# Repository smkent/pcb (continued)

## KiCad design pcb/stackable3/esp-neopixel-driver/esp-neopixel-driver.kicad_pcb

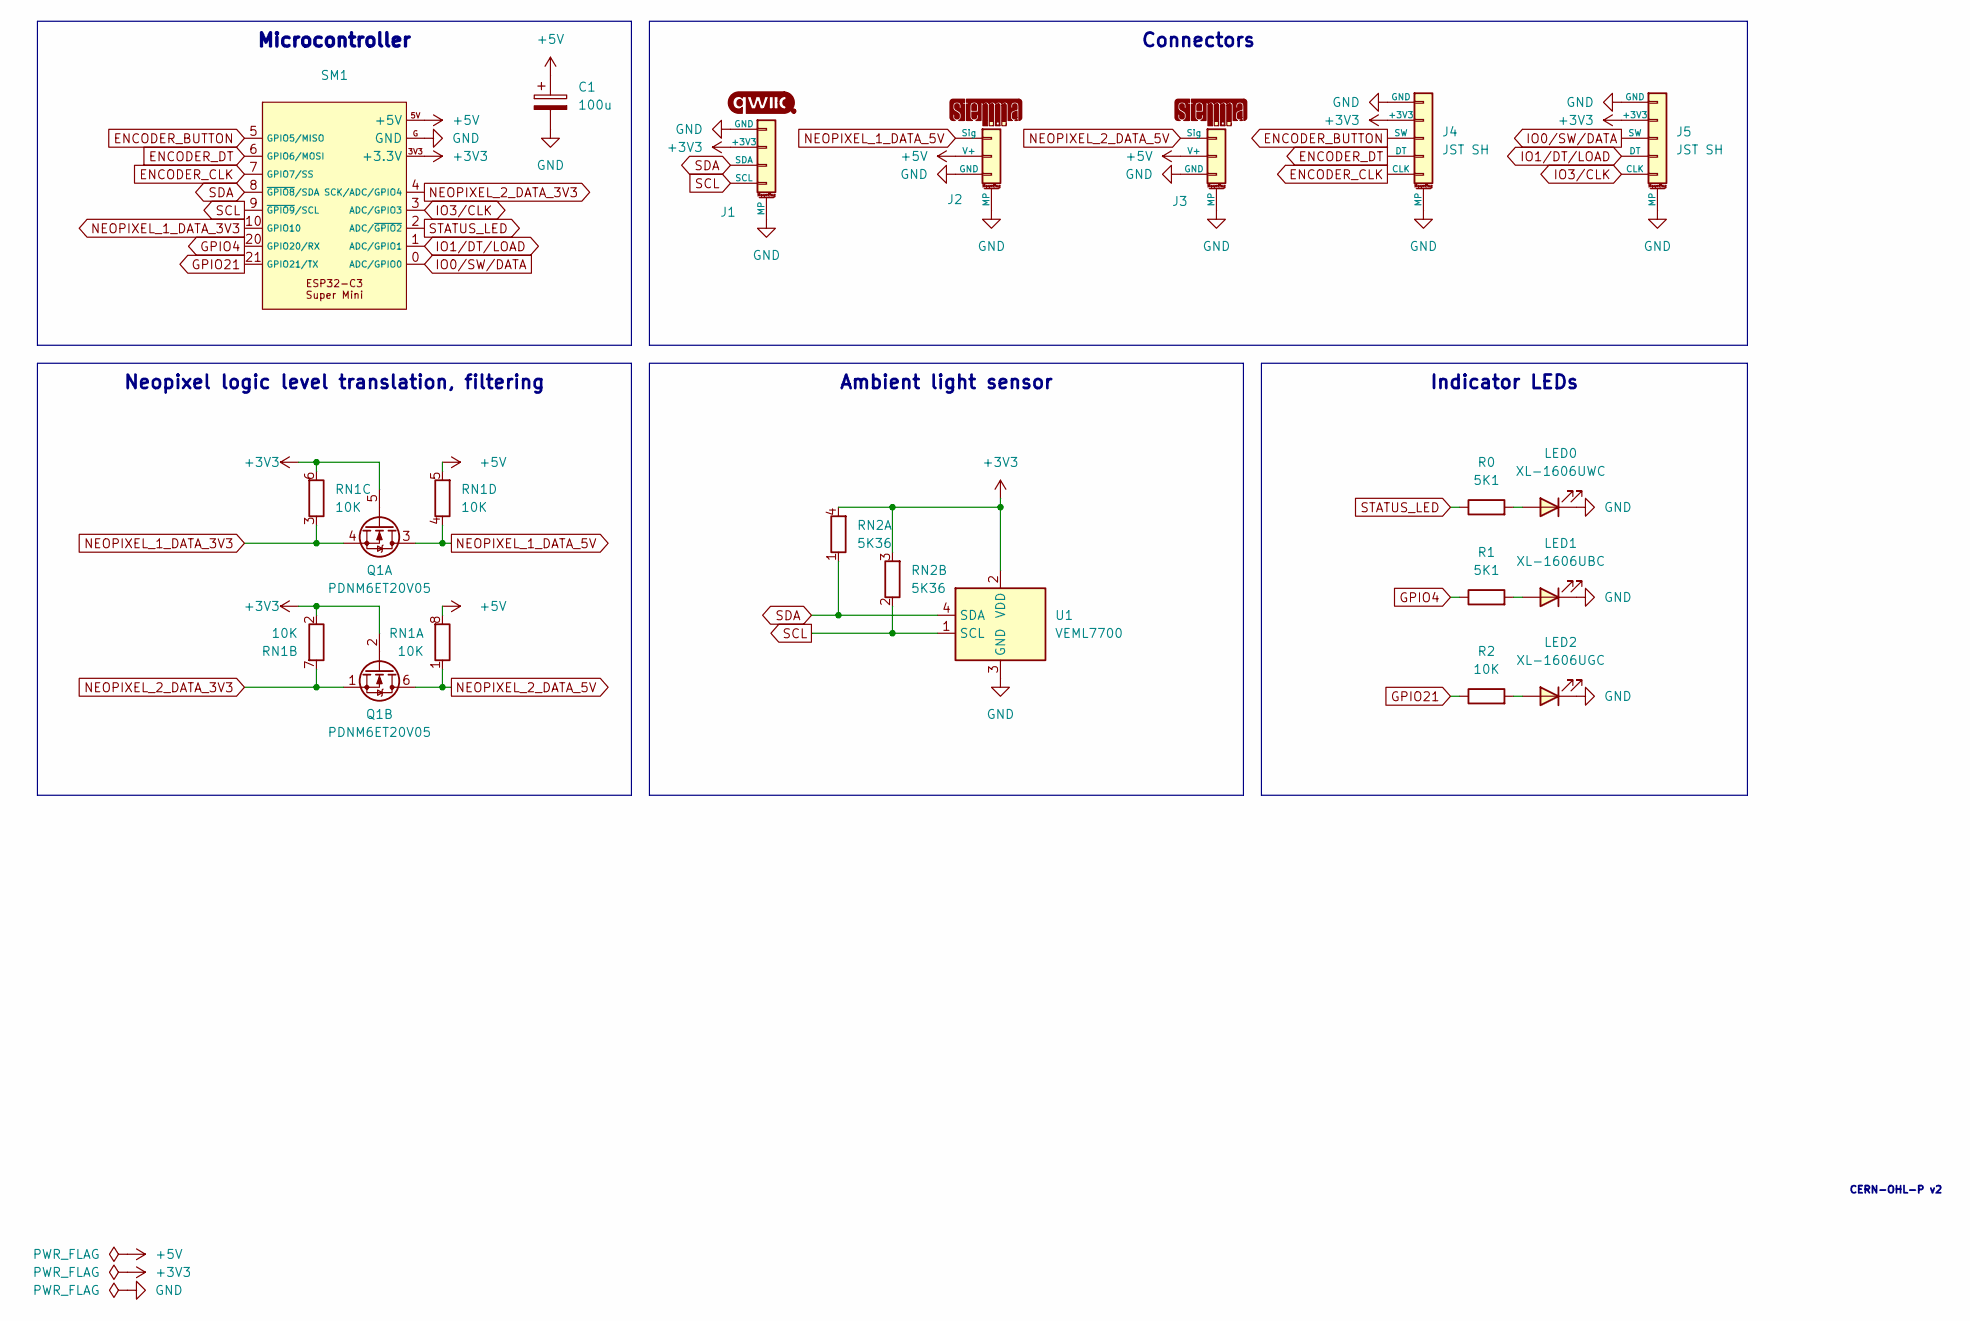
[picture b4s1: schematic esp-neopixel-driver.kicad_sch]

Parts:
C1: 100u; CP_Elec_5x5.4; LCSC Part C4054379
J1: Qwiic; Qwiic-SMD-horizontal-logo; LCSC Part C19270571
J2, J3: STEMMA-Signal; STEMMA-Signal-SMD-horizontal; LCSC Part C5372880
J4, J5: JST SH; JST_SH_SM05B-SRSS-TB_1x05-1MP_P1.00mm_Horizontal; LCSC Part C7433426
LED0: XL-1606UWC; LED_SideEmitter_1.7x1.1mm; LCSC Part C965866
LED1: XL-1606UBC; LED_SideEmitter_1.7x1.1mm; LCSC Part C965865
LED2: XL-1606UGC; LED_SideEmitter_1.7x1.1mm; LCSC Part C965863
Q1: PDNM6ET20V05; SOT-563; LCSC Part C918811
R0, R1: 5K1; R_0402_1005Metric; LCSC Part C25905
R2: 10K; R_0402_1005Metric; LCSC Part C25744
RN1: 10K; R_Array_Convex_4x0402; LCSC Part C7422173
RN2: 5K36; R_Array_Convex_2x0402; LCSC Part C425352
SM1: ESP32-C3-Super-Mini-Castellated-SMD-only
U1: VEML7700; Sensor_VEML7700-TR; LCSC Part C504893

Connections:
+3V3: J1.2 (+3V3), J4.2 (+3V3), J5.2 (+3V3), Q1.2 (G), Q1.5 (G), RN1.2 (R2.1), RN1.6 (R3.2), RN2.3 (R2.2), RN2.4 (R1.2), SM1.3V3 (+3.3V), U1.2 (VDD)
+5V: C1.1, J2.2 (V+), J3.2 (V+), RN1.5 (R4.2), RN1.8 (R1.2), SM1.5V (+5V)
ENCODER_BUTTON: J4.3 (SW), SM1.5 (GPIO5/MISO)
ENCODER_CLK: J4.5 (CLK), SM1.7 (GPIO7/SS)
ENCODER_DT: J4.4 (DT), SM1.6 (GPIO6/MOSI)
GND: C1.2, J1.1 (GND), J1.MP, J2.3 (GND), J2.MP, J3.3 (GND), J3.MP, J4.1 (GND), J4.MP, J5.1 (GND), J5.MP, LED0.1 (K), LED1.1 (K), LED2.1 (K), SM1.G (GND), U1.3 (GND)
GPIO4: R1.1, SM1.20 (GPIO20/RX)
GPIO21: R2.1, SM1.21 (GPIO21/TX)
IO0/SW/DATA: J5.3 (SW), SM1.0 (ADC/GPIO0)
IO1/DT/LOAD: J5.4 (DT), SM1.1 (ADC/GPIO1)
IO3/CLK: J5.5 (CLK), SM1.3 (ADC/GPIO3)
NEOPIXEL_1_DATA_3V3: Q1.4 (S), RN1.3 (R3.1), SM1.10 (GPIO10)
NEOPIXEL_1_DATA_5V: J2.1 (Sig), Q1.3 (D), RN1.4 (R4.1)
NEOPIXEL_2_DATA_3V3: Q1.1 (S), RN1.7 (R2.2), SM1.4 (SCK/ADC/GPIO4)
NEOPIXEL_2_DATA_5V: J3.1 (Sig), Q1.6 (D), RN1.1 (R1.1)
unnamed: LED0.2 (A), R0.2
unnamed: LED1.2 (A), R1.2
unnamed: LED2.2 (A), R2.2
SCL: J1.4 (SCL), RN2.2 (R2.1), SM1.9 (~GPIO9/SCL), U1.1 (SCL)
SDA: J1.3 (SDA), RN2.1 (R1.1), SM1.8 (~GPIO8/SDA), U1.4 (SDA)
STATUS_LED: R0.1, SM1.2 (ADC/~GPIO2)

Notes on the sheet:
Ambient light sensor
Connectors
Neopixel logic level translation, filtering
Indicator LEDs
Microcontroller
CERN-OHL-P v2

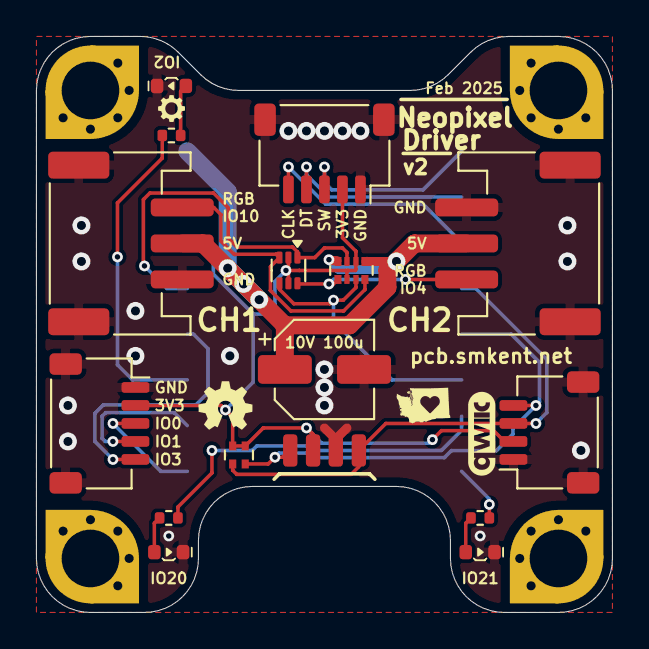
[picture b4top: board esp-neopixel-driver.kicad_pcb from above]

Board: 2 copper layers, 32.0 x 32.0 mm, 17 parts (1 on the bottom side), 21 nets.

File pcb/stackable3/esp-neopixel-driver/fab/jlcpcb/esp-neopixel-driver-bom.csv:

Comment,Designator,Footprint,LCSC
JST SH,"J4,J5",connector:JST_SH_SM05B-SRSS-TB_1x05-1MP_P1.00mm_Horizontal,C7433426
5K1,"R0,R1",Resistor_SMD:R_0402_1005Metric,C25905
XL-1606UWC,LED0,discrete:LED_SideEmitter_1.7x1.1mm,C965866
100u,C1,Capacitor_SMD:CP_Elec_5x5.4,C4054379
XL-1606UGC,LED2,discrete:LED_SideEmitter_1.7x1.1mm,C965863
Qwiic,J1,connector:Qwiic-SMD-horizontal-logo,C19270571
~,SM1,module:ESP32-C3-Super-Mini-Castellated-SMD-only,
5K36,RN2,Resistor_SMD:R_Array_Convex_2x0402, C425352
XL-1606UBC,LED1,discrete:LED_SideEmitter_1.7x1.1mm,C965865
10K,RN1,Resistor_SMD:R_Array_Convex_4x0402,C7422173
STEMMA-Signal,"J2,J3",connector:STEMMA-Signal-SMD-horizontal,C5372880
PDNM6ET20V05,Q1,Package_TO_SOT_SMD:SOT-563,C918811
VEML7700,U1,discrete:Sensor_VEML7700-TR,C504893
10K,R2,Resistor_SMD:R_0402_1005Metric,C25744

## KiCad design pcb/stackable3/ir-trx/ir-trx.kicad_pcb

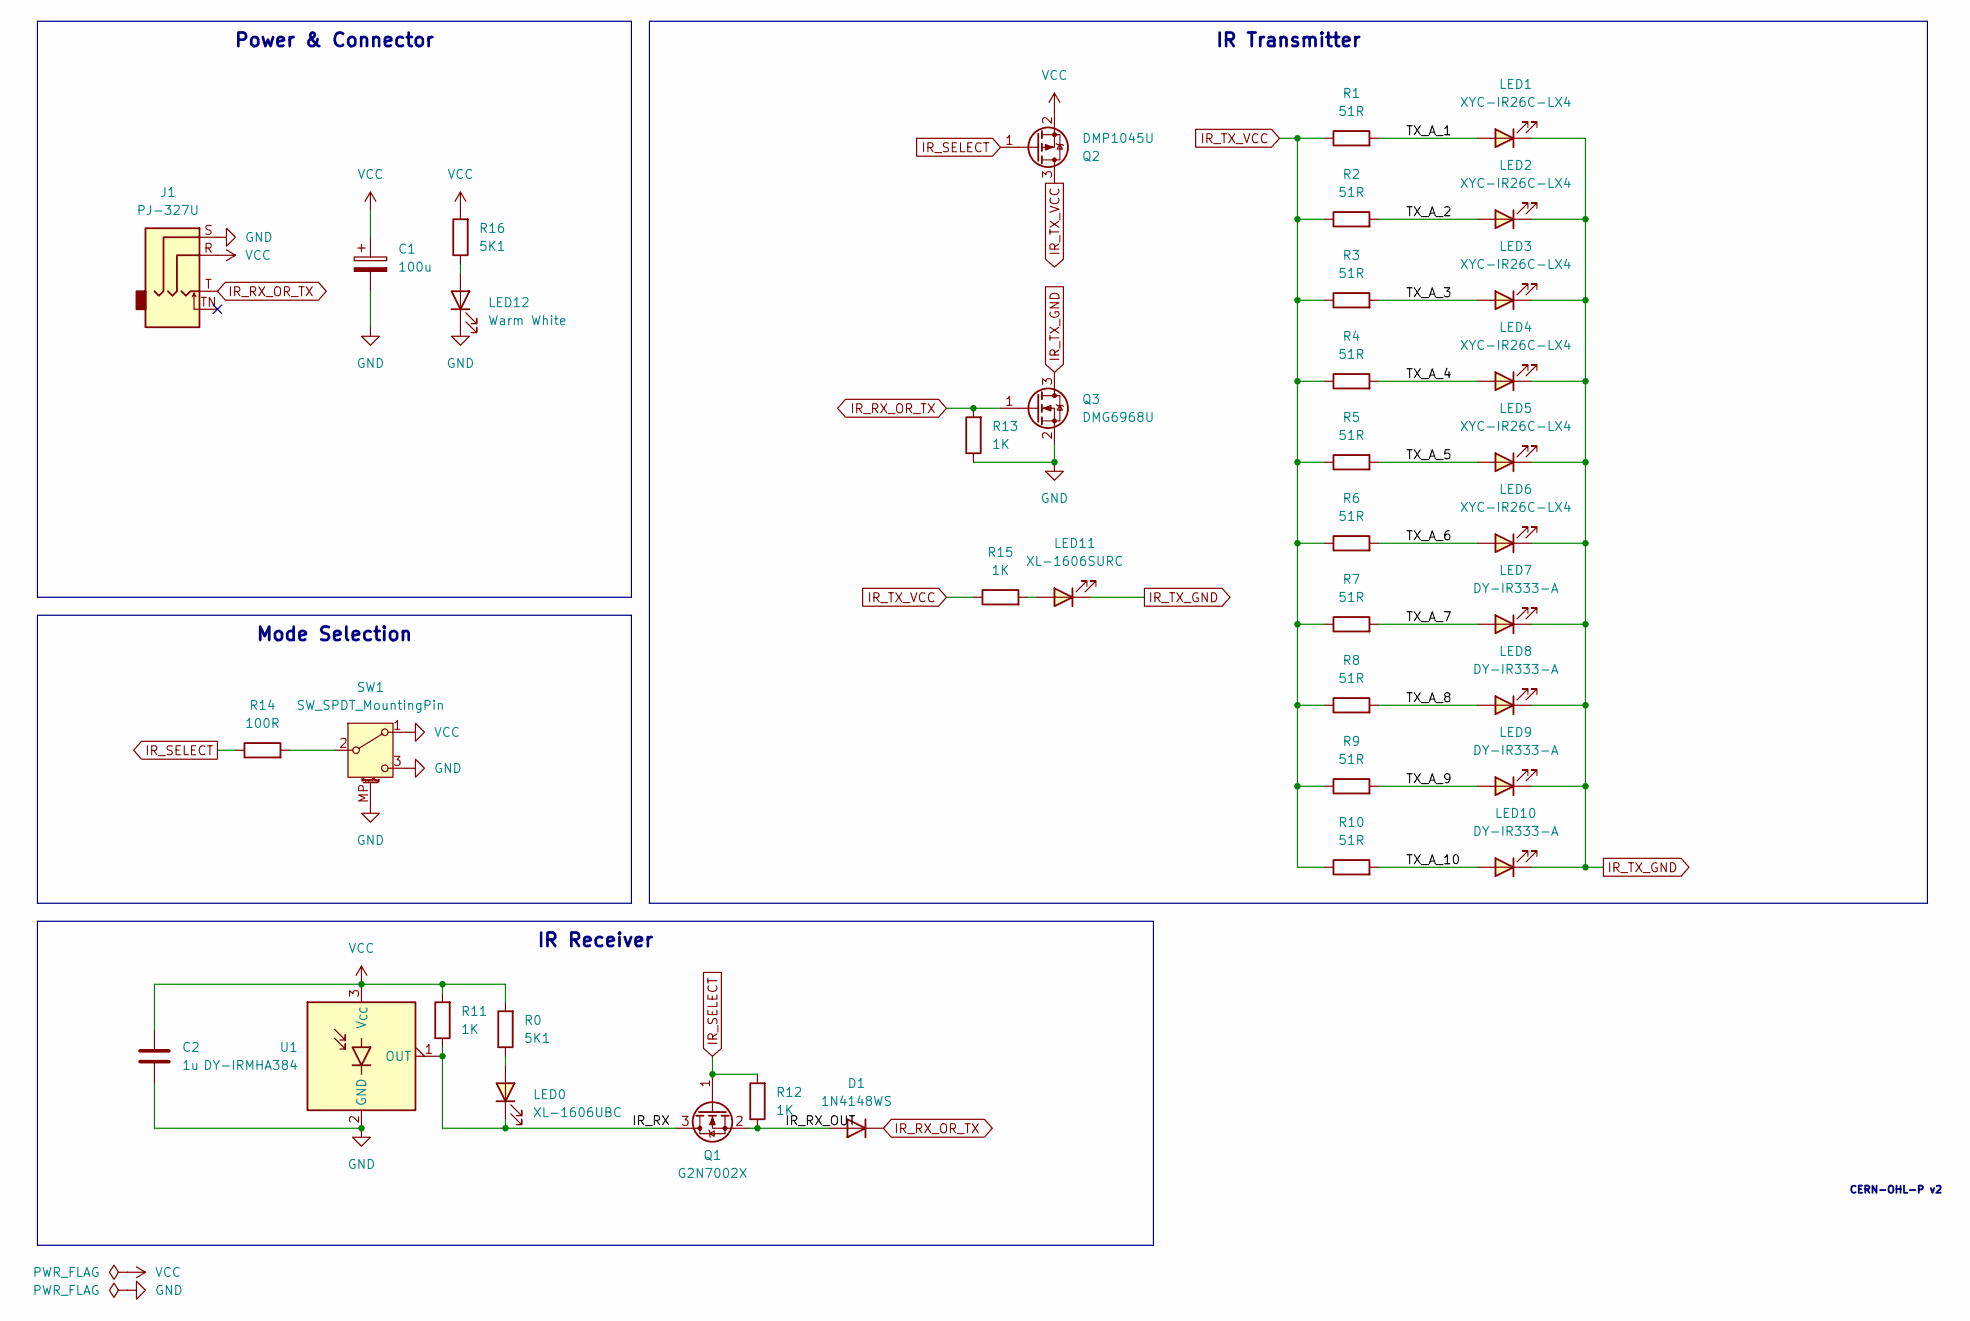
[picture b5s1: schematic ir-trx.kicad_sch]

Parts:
C1: 100u; CP_Elec_5x5.4
C2: 1u; C_0402_1005Metric
D1: 1N4148WS; D_SOD-323
J1: PJ-327U; Jack_3.5mm_PJ-327U-SMT_Horizontal_EdgeCut; LCSC Part C397453
LED0: XL-1606UBC; LED_SideEmitter_1.7x1.1mm; LCSC Part C965865
LED1, LED2, LED3, LED4, LED5, LED6: XYC-IR26C-LX4; LED_IR_SideEmitter_1206_3216Metric; LCSC Part C396674
LED7, LED8, LED9, LED10: DY-IR333-A; LED_D5.0mm_IRGrey; LCSC Part C396674
LED11: XL-1606SURC; LED_SideEmitter_1.7x1.1mm; LCSC Part C965860
LED12: Warm White; LED_0603_1608Metric
Q1: G2N7002X; SOT-523; LCSC Part C5258971
Q2: DMP1045U; SOT-23; LCSC Part C177033
Q3: DMG6968U; SOT-23; LCSC Part C150759
R0, R16: 5K1; R_0402_1005Metric
R1, R2, R3, R4, R5, R6, R7, R8, R9, R10: 51R; R_1206_3216Metric
R11, R12, R13, R15: 1K; R_0402_1005Metric
R14: 100R; R_0603_1608Metric
SW1: SW_SPDT_MountingPin; SW_Slide_SPDT_Straight_CK_OS102011MS2Q
U1: DY-IRMHA384; IRM_5.0mmx4.2mm_P1.27mm_Horizontal; LCSC Part C6071554

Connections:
/IR_RX: LED0.1 (K), Q1.3 (D), R11.1, U1.1 (OUT)
/IR_RX_OUT: D1.2 (A), Q1.2 (S), R12.1
/TX_A_1: LED1.2 (A), R1.2
/TX_A_2: LED2.2 (A), R2.2
/TX_A_3: LED3.2 (A), R3.2
/TX_A_4: LED4.2 (A), R4.2
/TX_A_5: LED5.2 (A), R5.2
/TX_A_6: LED6.2 (A), R6.2
/TX_A_7: LED7.2 (A), R7.2
/TX_A_8: LED8.2 (A), R8.2
/TX_A_9: LED9.2 (A), R9.2
/TX_A_10: LED10.2 (A), R10.2
GND: C1.2, C2.2, J1.S, LED12.1 (K), Q3.2 (S), R13.1, SW1.3 (C), SW1.MP (MountPin), U1.2 (GND)
IR_RX_OR_TX: D1.1 (K), J1.T, Q3.1 (G), R13.2
IR_SELECT: Q1.1 (G), Q2.1 (G), R12.2, R14.1
IR_TX_GND: LED1.1 (K), LED2.1 (K), LED3.1 (K), LED4.1 (K), LED5.1 (K), LED6.1 (K), LED7.1 (K), LED8.1 (K), LED9.1 (K), LED10.1 (K), LED11.1 (K), Q3.3 (D)
IR_TX_VCC: Q2.3 (D), R1.1, R2.1, R3.1, R4.1, R5.1, R6.1, R7.1, R8.1, R9.1, R10.1, R15.1
unnamed: LED0.2 (A), R0.1
unnamed: LED11.2 (A), R15.2
unnamed: LED12.2 (A), R16.1
unnamed: R14.2, SW1.2 (B)
VCC: C1.1, C2.1, J1.R, Q2.2 (S), R0.2, R11.2, R16.2, SW1.1 (A), U1.3 (V_{CC})

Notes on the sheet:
Power & Connector
Mode Selection
IR Receiver
IR Transmitter
CERN-OHL-P v2

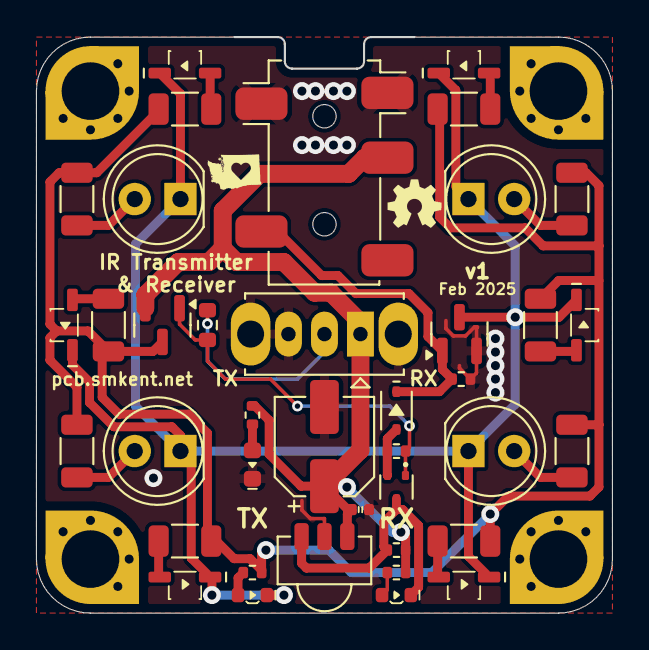
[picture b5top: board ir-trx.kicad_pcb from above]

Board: 2 copper layers, 32.0 x 32.0 mm, 39 parts (0 on the bottom side), 22 nets.

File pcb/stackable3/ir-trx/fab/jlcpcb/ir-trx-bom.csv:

Comment,Designator,Footprint,LCSC
51R,"R1,R2,R3,R4,R5,R6,R7,R8,R9,R10",Resistor_SMD:R_1206_3216Metric,C149687
PJ-327U,J1,connector:Jack_3.5mm_PJ-327U-SMT_Horizontal_EdgeCut,C397453
1N4148WS,D1,package:D_SOD-323,
SW_SPDT_MountingPin,SW1,electromechanical:SW_Slide_SPDT_Straight_CK_OS102011MS2Q,
DMG6968U,Q3,Package_TO_SOT_SMD:SOT-23,C150759
1K,"R11,R12,R13,R15",Resistor_SMD:R_0402_1005Metric,
DY-IR333-A,"LED7,LED8,LED9,LED10",LED_THT:LED_D5.0mm_IRGrey,C396674
DMP1045U,Q2,Package_TO_SOT_SMD:SOT-23,C177033
100u,C1,Capacitor_SMD:CP_Elec_5x5.4,
G2N7002X,Q1,package:SOT-523,C5258971
DY-IRMHA384,U1,package:IRM_5.0mmx4.2mm_P1.27mm_Horizontal,C6071554
XL-1606SURC,LED11,discrete:LED_SideEmitter_1.7x1.1mm,C965860
100R,R14,Resistor_SMD:R_0603_1608Metric,
5K1,"R0,R16",Resistor_SMD:R_0402_1005Metric,
XYC-IR26C-LX4,"LED1,LED2,LED3,LED4,LED5,LED6",discrete:LED_IR_SideEmitter_1206_3216Metric,C396674
XL-1606UBC,LED0,discrete:LED_SideEmitter_1.7x1.1mm,C965865
Warm White,LED12,discrete:LED_0603_1608Metric,
1u,C2,discrete:C_0402_1005Metric,

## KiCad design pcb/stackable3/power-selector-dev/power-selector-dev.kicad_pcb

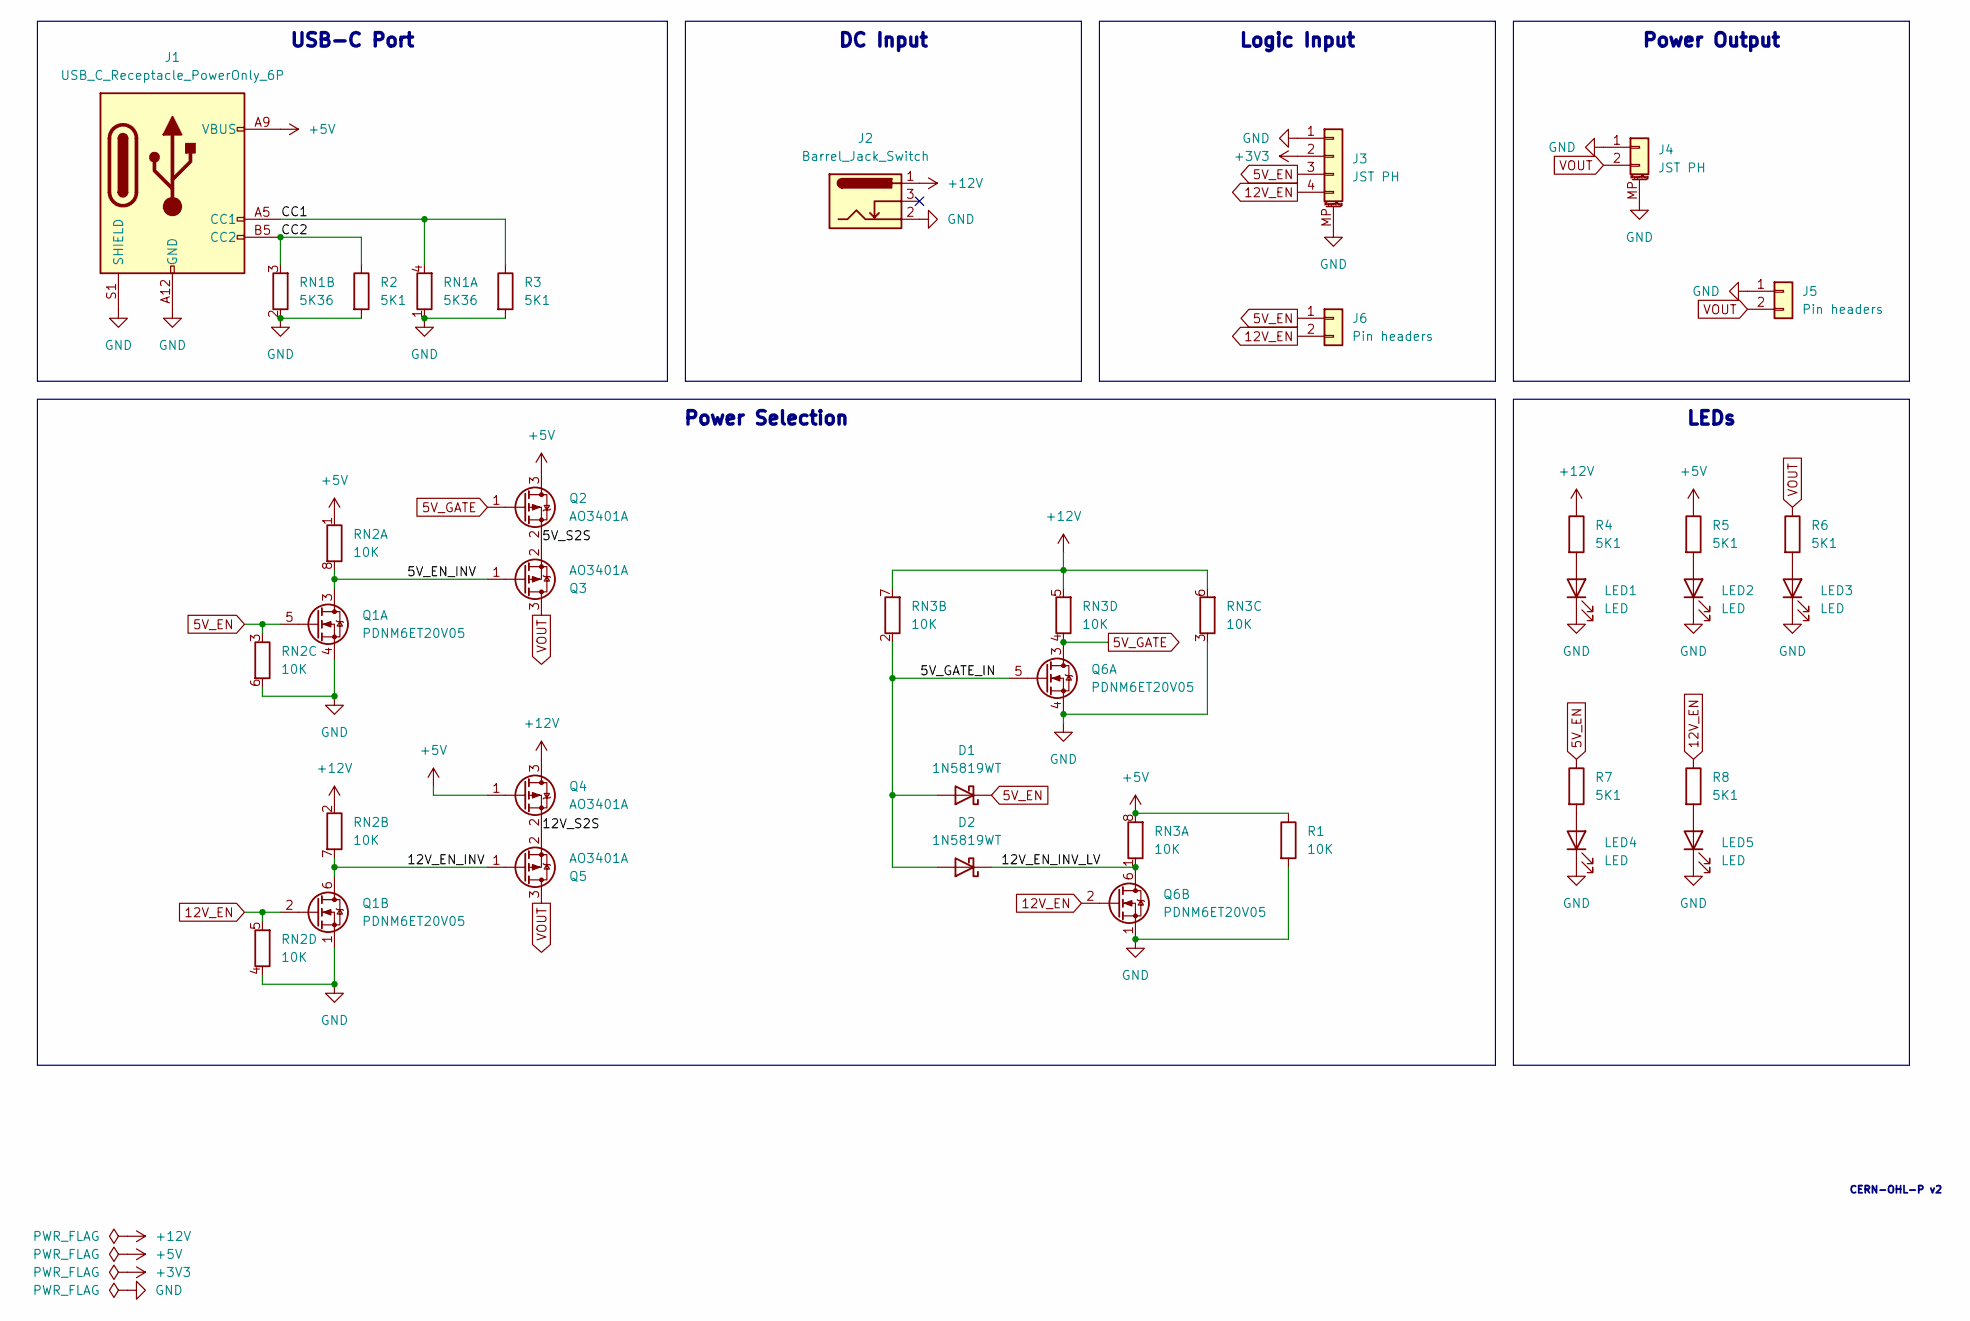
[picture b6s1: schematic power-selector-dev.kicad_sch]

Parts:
D1, D2: 1N5819WT; D_SOD-523; LCSC Part C20754784
J1: USB_C_Receptacle_PowerOnly_6P; USB_C_Receptacle_GCT_USB4125-xx-x_6P_TopMnt_Horizontal_Hand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; LCSC Part C2927029
J2: Barrel_Jack_Switch; BarrelJack_DC-050_SMT_Horizontal
J3: JST PH; JST_PH_S4B-PH-SM4-TB_1x04-1MP_P2.00mm_Horizontal
J4: JST PH; JST_PH_S2B-PH-SM4-TB_1x02-1MP_P2.00mm_Horizontal
J5, J6: Pin headers; PinHeader_1x02_P2.54mm_Vertical_simple
LED1, LED2, LED3, LED4, LED5: LED; LED_0603_1608Metric
Q1, Q6: PDNM6ET20V05; SOT-563; LCSC Part C918811
Q2, Q3, Q4, Q5: AO3401A; SOT-23
R1: 10K; R_0402_1005Metric
R2, R3, R4, R5, R6: 5K1; R_0603_1608Metric
R7, R8: 5K1; R_0402_1005Metric
RN1: 5K36; R_Array_Convex_2x0402
RN2, RN3: 10K; R_Array_Convex_4x0402

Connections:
5V_EN: D1.1 (K), J3.3, J6.1, Q1.5 (G), R7.1, RN2.3 (R3.1)
5V_GATE: Q2.1 (G), Q6.3 (D), RN3.4 (R4.1)
12V_EN: J3.4, J6.2, Q1.2 (G), Q6.2 (G), R8.1, RN2.5 (R4.2)
+3V3: J3.2
+5V: J1.A9 (VBUS), J1.B9 (VBUS), Q2.3 (D), Q4.1 (G), R1.1, R5.1, RN2.1 (R1.1), RN3.8 (R1.2)
+12V: J2.1, Q4.3 (D), R4.1, RN2.2 (R2.1), RN3.5 (R4.2), RN3.6 (R3.2), RN3.7 (R2.2)
/5V_EN_INV: Q1.3 (D), Q3.1 (G), RN2.8 (R1.2)
/5V_GATE_IN: D1.2 (A), D2.2 (A), Q6.5 (G), RN3.2 (R2.1)
/5V_S2S: Q2.2 (S), Q3.2 (S)
/12V_EN_INV: Q1.6 (D), Q5.1 (G), RN2.7 (R2.2)
/12V_EN_INV_LV: D2.1 (K), Q6.6 (D), RN3.1 (R1.1)
/12V_S2S: Q4.2 (S), Q5.2 (S)
/CC1: J1.A5 (CC1), R3.1, RN1.4 (R1.2)
/CC2: J1.B5 (CC2), R2.1, RN1.3 (R2.2)
GND: J1.A12 (GND), J1.B12 (GND), J1.S1 (SHIELD), J2.2, J3.1, J3.MP (MountPin), J4.1, J4.MP (MountPin), J5.1, LED1.1 (K), LED2.1 (K), LED3.1 (K), LED4.1 (K), LED5.1 (K), Q1.1 (S), Q1.4 (S), Q6.1 (S), Q6.4 (S), R1.2, R2.2, R3.2, RN1.1 (R1.1), RN1.2 (R2.1), RN2.4 (R4.1), RN2.6 (R3.2), RN3.3 (R3.1)
unnamed: LED1.2 (A), R4.2
unnamed: LED2.2 (A), R5.2
unnamed: LED3.2 (A), R6.2
unnamed: LED4.2 (A), R7.2
unnamed: LED5.2 (A), R8.2
VOUT: J4.2, J5.2, Q3.3 (D), Q5.3 (D), R6.1

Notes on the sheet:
Logic Input
DC Input
Power Output
USB-C Port
Power Selection
LEDs
CERN-OHL-P v2

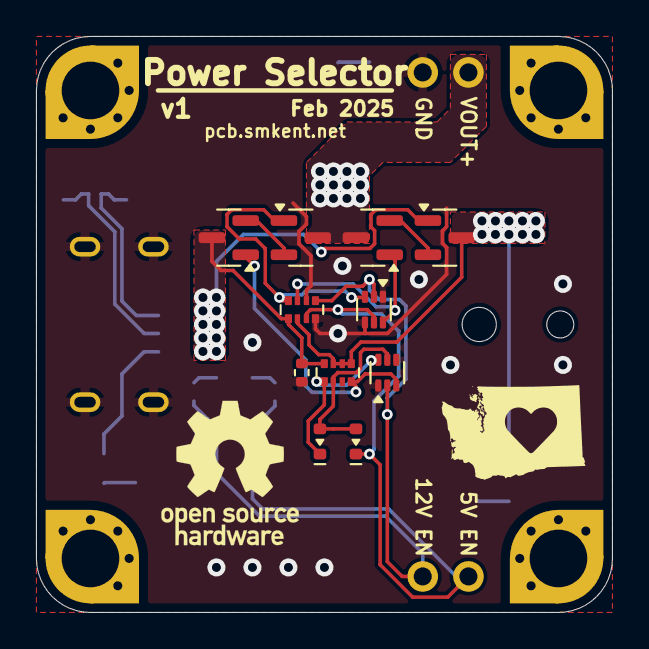
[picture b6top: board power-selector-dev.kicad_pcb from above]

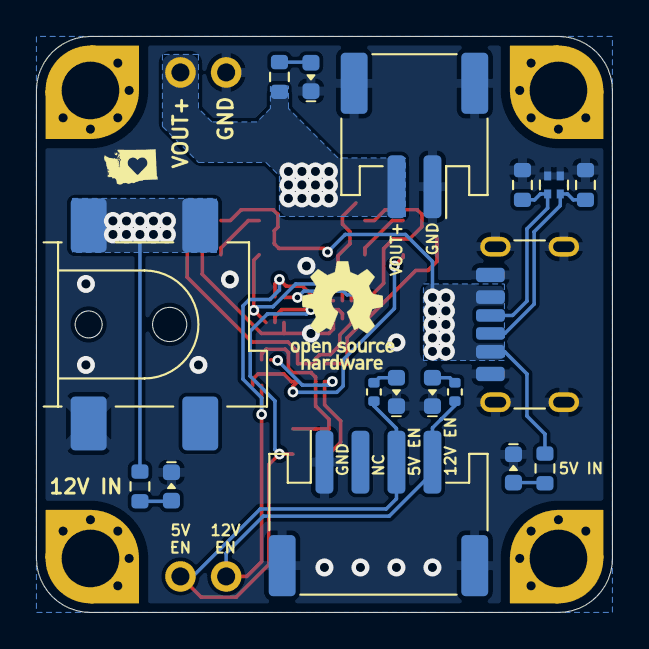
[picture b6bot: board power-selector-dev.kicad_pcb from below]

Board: 2 copper layers, 32.0 x 32.0 mm, 30 parts (19 on the bottom side), 20 nets.

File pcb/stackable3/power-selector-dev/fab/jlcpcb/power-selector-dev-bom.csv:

Comment,Designator,Footprint,LCSC
5K1,"R7,R8",Resistor_SMD:R_0402_1005Metric,
PDNM6ET20V05,"Q1,Q6",Package_TO_SOT_SMD:SOT-563,C918811
10K,"RN2,RN3",discrete:R_Array_Convex_4x0402,
1N5819WT,"D1,D2",package:D_SOD-523,C20754784
Barrel_Jack_Switch,J2,connector:BarrelJack_DC-050_SMT_Horizontal,
5K1,"R2,R3,R4,R5,R6",Resistor_SMD:R_0603_1608Metric,
LED,"LED1,LED2,LED3,LED4,LED5",discrete:LED_0603_1608Metric,
Pin headers,"J5,J6",custom:PinHeader_1x02_P2.54mm_Vertical_simple,
10K,R1,Resistor_SMD:R_0402_1005Metric,
AO3401A,"Q2,Q3,Q4,Q5",Package_TO_SOT_SMD:SOT-23,
USB_C_Receptacle_PowerOnly_6P,J1,connector:USB_C_Receptacle_GCT_USB4125-xx-x_6P_TopMnt_Horizontal_HandSolder,C2927029
JST PH,J4,connector:JST_PH_S2B-PH-SM4-TB_1x02-1MP_P2.00mm_Horizontal,
JST PH,J3,connector:JST_PH_S4B-PH-SM4-TB_1x04-1MP_P2.00mm_Horizontal,
5K36,RN1,Resistor_SMD:R_Array_Convex_2x0402,

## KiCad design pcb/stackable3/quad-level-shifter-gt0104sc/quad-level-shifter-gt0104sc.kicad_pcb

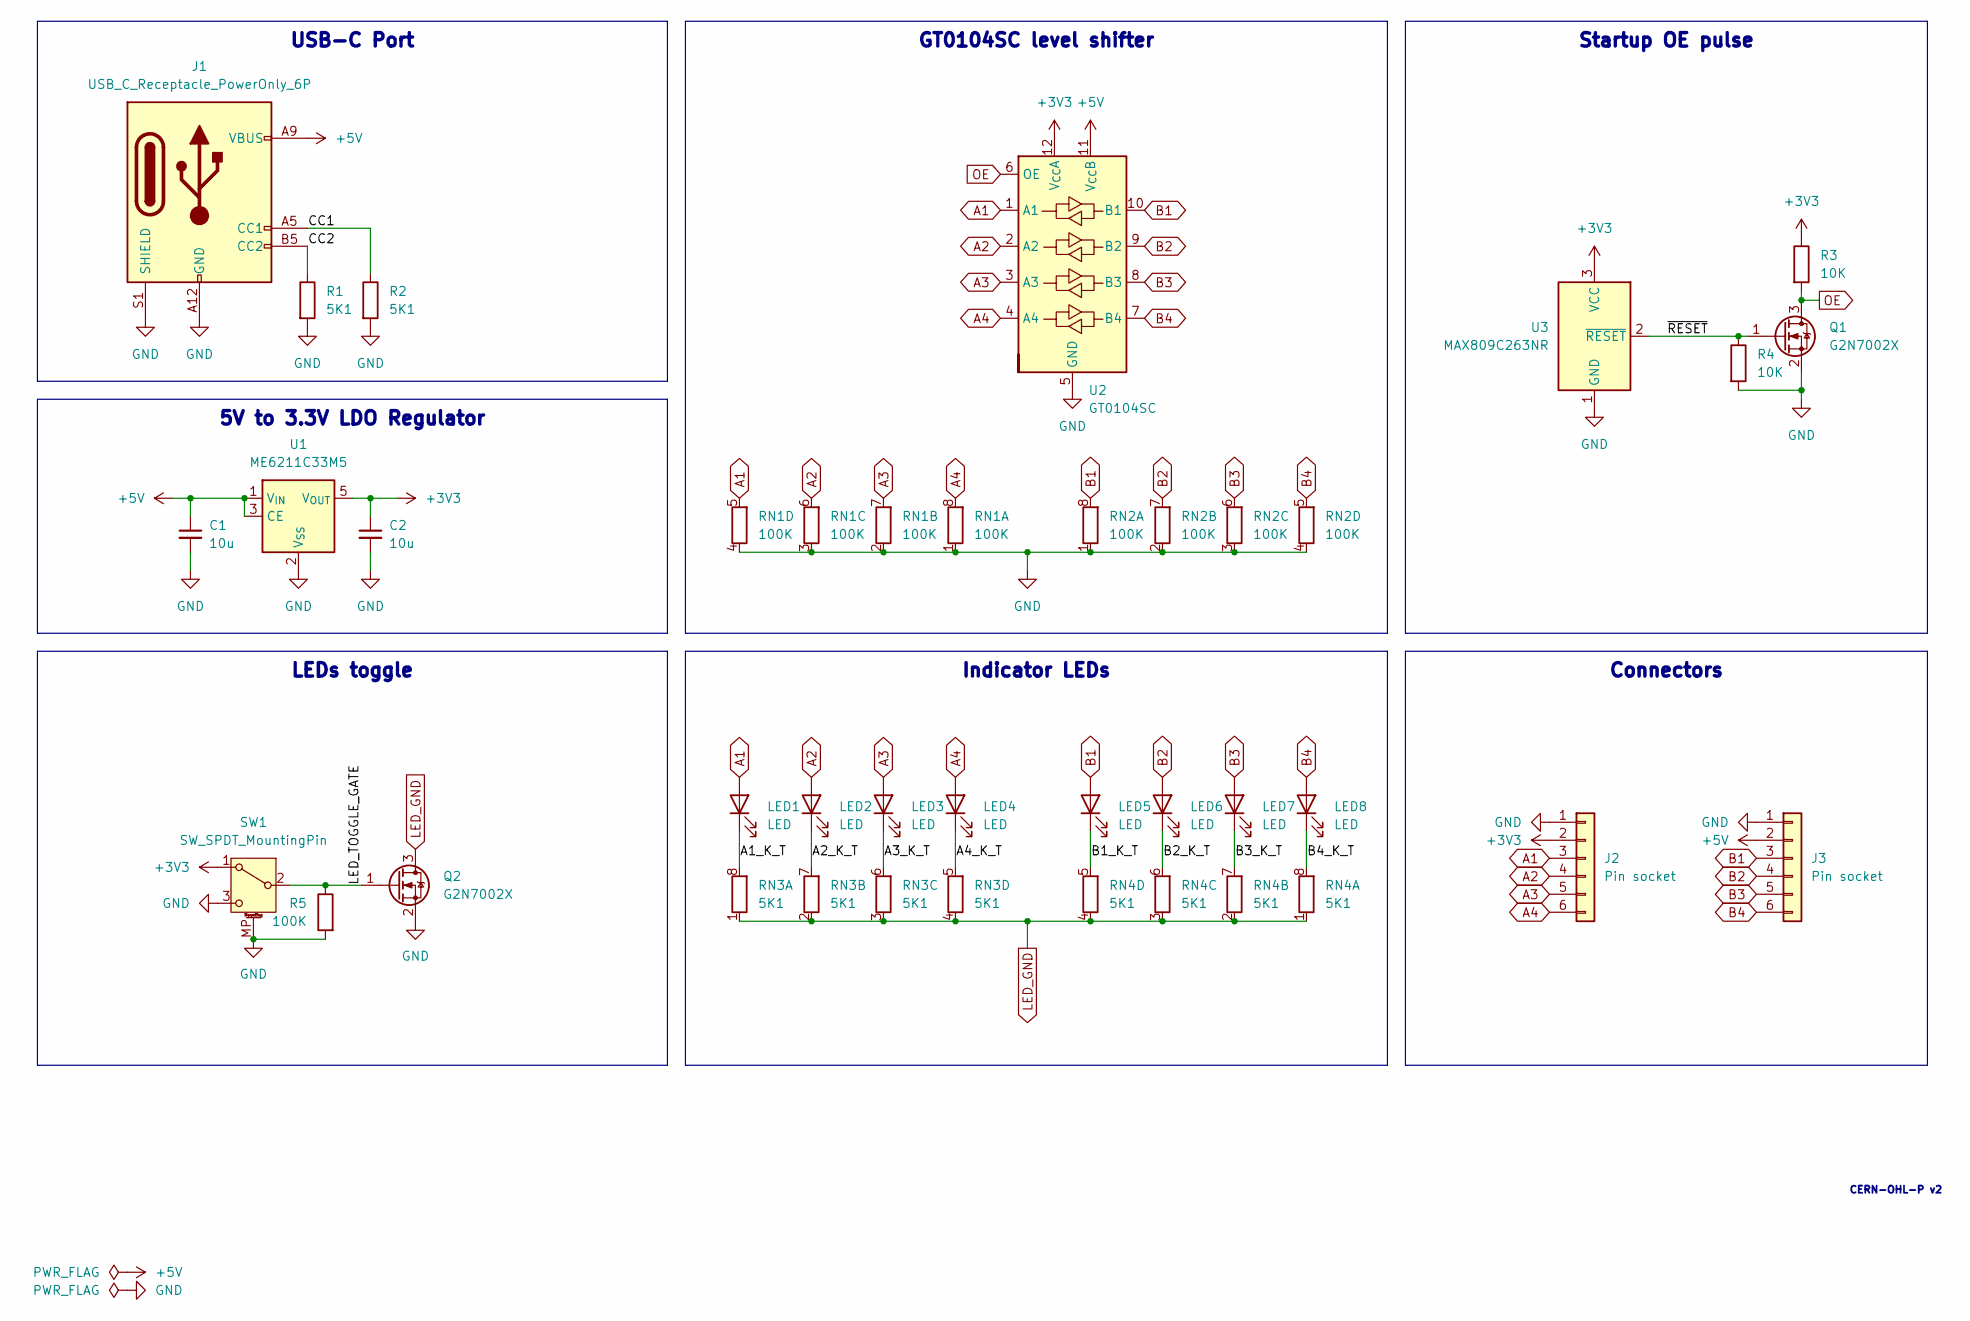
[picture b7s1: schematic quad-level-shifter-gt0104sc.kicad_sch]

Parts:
C1, C2: 10u; C_0402_1005Metric; LCSC Part C315248
J1: USB_C_Receptacle_PowerOnly_6P; USB_C_Receptacle_GCT_USB4125-xx-x_6P_TopMnt_Horizontal_Hand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; LCSC Part C2927029
J2, J3: Pin socket; PinSocket_1x06_P2.54mm_Vertical
LED1, LED2, LED3, LED4, LED5, LED6, LED7, LED8: LED; LED_0603_1608Metric
Q1, Q2: G2N7002X; SOT-523; LCSC Part C5258971
R1, R2: 5K1; R_0603_1608Metric; LCSC Part C23186
R3, R4: 10K; R_0402_1005Metric; LCSC Part C25744
R5: 100K; R_0402_1005Metric; LCSC Part C25741
RN1, RN2: 100K; R_Array_Convex_4x0402_HandSolder; LCSC Part C326786
RN3, RN4: 5K1; R_Array_Convex_4x0402_HandSolder; LCSC Part C425290
SW1: SW_SPDT_MountingPin; SW_SPDT_PCM12; LCSC Part C319020
U1: ME6211C33M5; SOT-23-5; LCSC Part C82942
U2: GT0104SC; QFN-12-1EP_2x2mm_P0.4mm_EP1.1x1.1mm; LCSC Part C22356898
U3: MAX809C263NR; SOT-23; LCSC Part C5223646

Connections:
+3V3: C2.1, J2.2, R3.1, SW1.1 (A), U1.5 (V_{OUT}), U2.12 (V_{CC}A), U3.3 (VCC)
+5V: C1.1, J1.A9 (VBUS), J1.B9 (VBUS), J3.2, U1.1 (V_{IN}), U1.3 (CE), U2.11 (V_{CC}B)
/A1_K_T: LED1.1 (K), RN3.8 (R1.2)
/A2_K_T: LED2.1 (K), RN3.7 (R2.2)
/A3_K_T: LED3.1 (K), RN3.6 (R3.2)
/A4_K_T: LED4.1 (K), RN3.5 (R4.2)
/B1_K_T: LED5.1 (K), RN4.5 (R4.2)
/B2_K_T: LED6.1 (K), RN4.6 (R3.2)
/B3_K_T: LED7.1 (K), RN4.7 (R2.2)
/B4_K_T: LED8.1 (K), RN4.8 (R1.2)
/CC1: J1.A5 (CC1), R2.1
/CC2: J1.B5 (CC2), R1.1
/LED_TOGGLE_GATE: Q2.1 (G), R5.1, SW1.2 (B)
/~RESET: Q1.1 (G), R4.1, U3.2 (~RESET)
A1: J2.3, LED1.2 (A), RN1.5 (R4.2), U2.1 (A1)
A2: J2.4, LED2.2 (A), RN1.6 (R3.2), U2.2 (A2)
A3: J2.5, LED3.2 (A), RN1.7 (R2.2), U2.3 (A3)
A4: J2.6, LED4.2 (A), RN1.8 (R1.2), U2.4 (A4)
B1: J3.3, LED5.2 (A), RN2.8 (R1.2), U2.10 (B1)
B2: J3.4, LED6.2 (A), RN2.7 (R2.2), U2.9 (B2)
B3: J3.5, LED7.2 (A), RN2.6 (R3.2), U2.8 (B3)
B4: J3.6, LED8.2 (A), RN2.5 (R4.2), U2.7 (B4)
GND: C1.2, C2.2, J1.A12 (GND), J1.B12 (GND), J1.S1 (SHIELD), J2.1, J3.1, Q1.2 (S), Q2.2 (S), R1.2, R2.2, R4.2, R5.2, RN1.1 (R1.1), RN1.2 (R2.1), RN1.3 (R3.1), RN1.4 (R4.1), RN2.1 (R1.1), RN2.2 (R2.1), RN2.3 (R3.1), RN2.4 (R4.1), SW1.3 (C), SW1.MP (MountPin), U1.2 (V_{SS}), U2.5 (GND), U2.13 (Pad), U3.1 (GND)
LED_GND: Q2.3 (D), RN3.1 (R1.1), RN3.2 (R2.1), RN3.3 (R3.1), RN3.4 (R4.1), RN4.1 (R1.1), RN4.2 (R2.1), RN4.3 (R3.1), RN4.4 (R4.1)
OE: Q1.3 (D), R3.2, U2.6 (OE)

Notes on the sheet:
Connectors
Indicator LEDs
GT0104SC level shifter
5V to 3.3V LDO Regulator
Startup OE pulse
LEDs toggle
USB-C Port
CERN-OHL-P v2

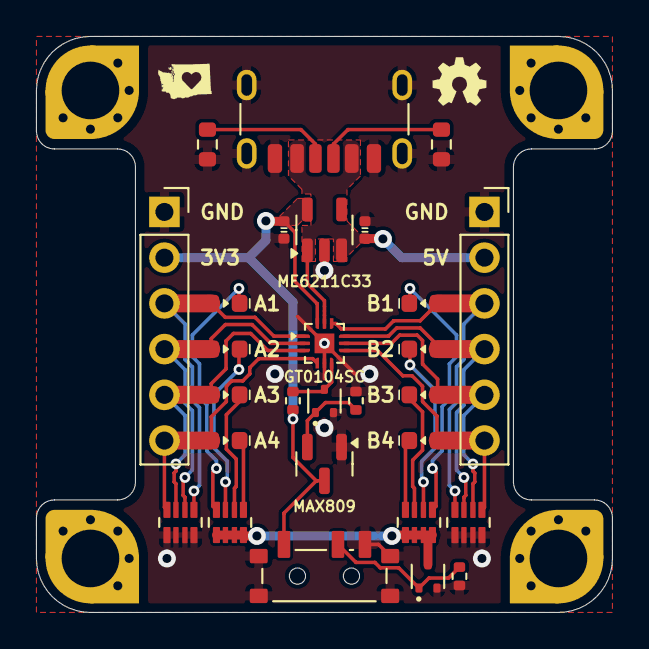
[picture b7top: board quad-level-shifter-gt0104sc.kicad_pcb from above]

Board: 2 copper layers, 32.0 x 32.0 mm, 28 parts (0 on the bottom side), 25 nets.

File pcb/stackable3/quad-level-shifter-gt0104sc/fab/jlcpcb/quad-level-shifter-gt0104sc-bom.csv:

Comment,Designator,Footprint,LCSC
LED,"LED1,LED2,LED3,LED4,LED5,LED6,LED7,LED8",discrete:LED_0603_1608Metric,
5K1,"RN3,RN4",discrete:R_Array_Convex_4x0402_HandSolder,C425290
Pin socket,"J2,J3",Connector_PinSocket_2.54mm:PinSocket_1x06_P2.54mm_Vertical,
10u,"C1,C2",discrete:C_0402_1005Metric,C315248
ME6211C33M5,U1,Package_TO_SOT_SMD:SOT-23-5,C82942
G2N7002X,"Q1,Q2",package:SOT-523,C5258971
100K,"RN1,RN2",discrete:R_Array_Convex_4x0402_HandSolder,C326786
MAX809C263NR,U3,Package_TO_SOT_SMD:SOT-23,C5223646
10K,"R3,R4",Resistor_SMD:R_0402_1005Metric,C25744
100K,R5,Resistor_SMD:R_0402_1005Metric,C25741
SW_SPDT_MountingPin,SW1,electromechanical:SW_SPDT_PCM12,C319020
5K1,"R1,R2",Resistor_SMD:R_0603_1608Metric,C23186
USB_C_Receptacle_PowerOnly_6P,J1,connector:USB_C_Receptacle_GCT_USB4125-xx-x_6P_TopMnt_Horizontal_HandSolder,C2927029
GT0104SC,U2,package:QFN-12-1EP_2x2mm_P0.4mm_EP1.1x1.1mm,C22356898
